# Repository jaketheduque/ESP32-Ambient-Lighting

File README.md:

Check out the project website here: https://jaketheduque.github.io/ESP32-Ambient-Lighting/

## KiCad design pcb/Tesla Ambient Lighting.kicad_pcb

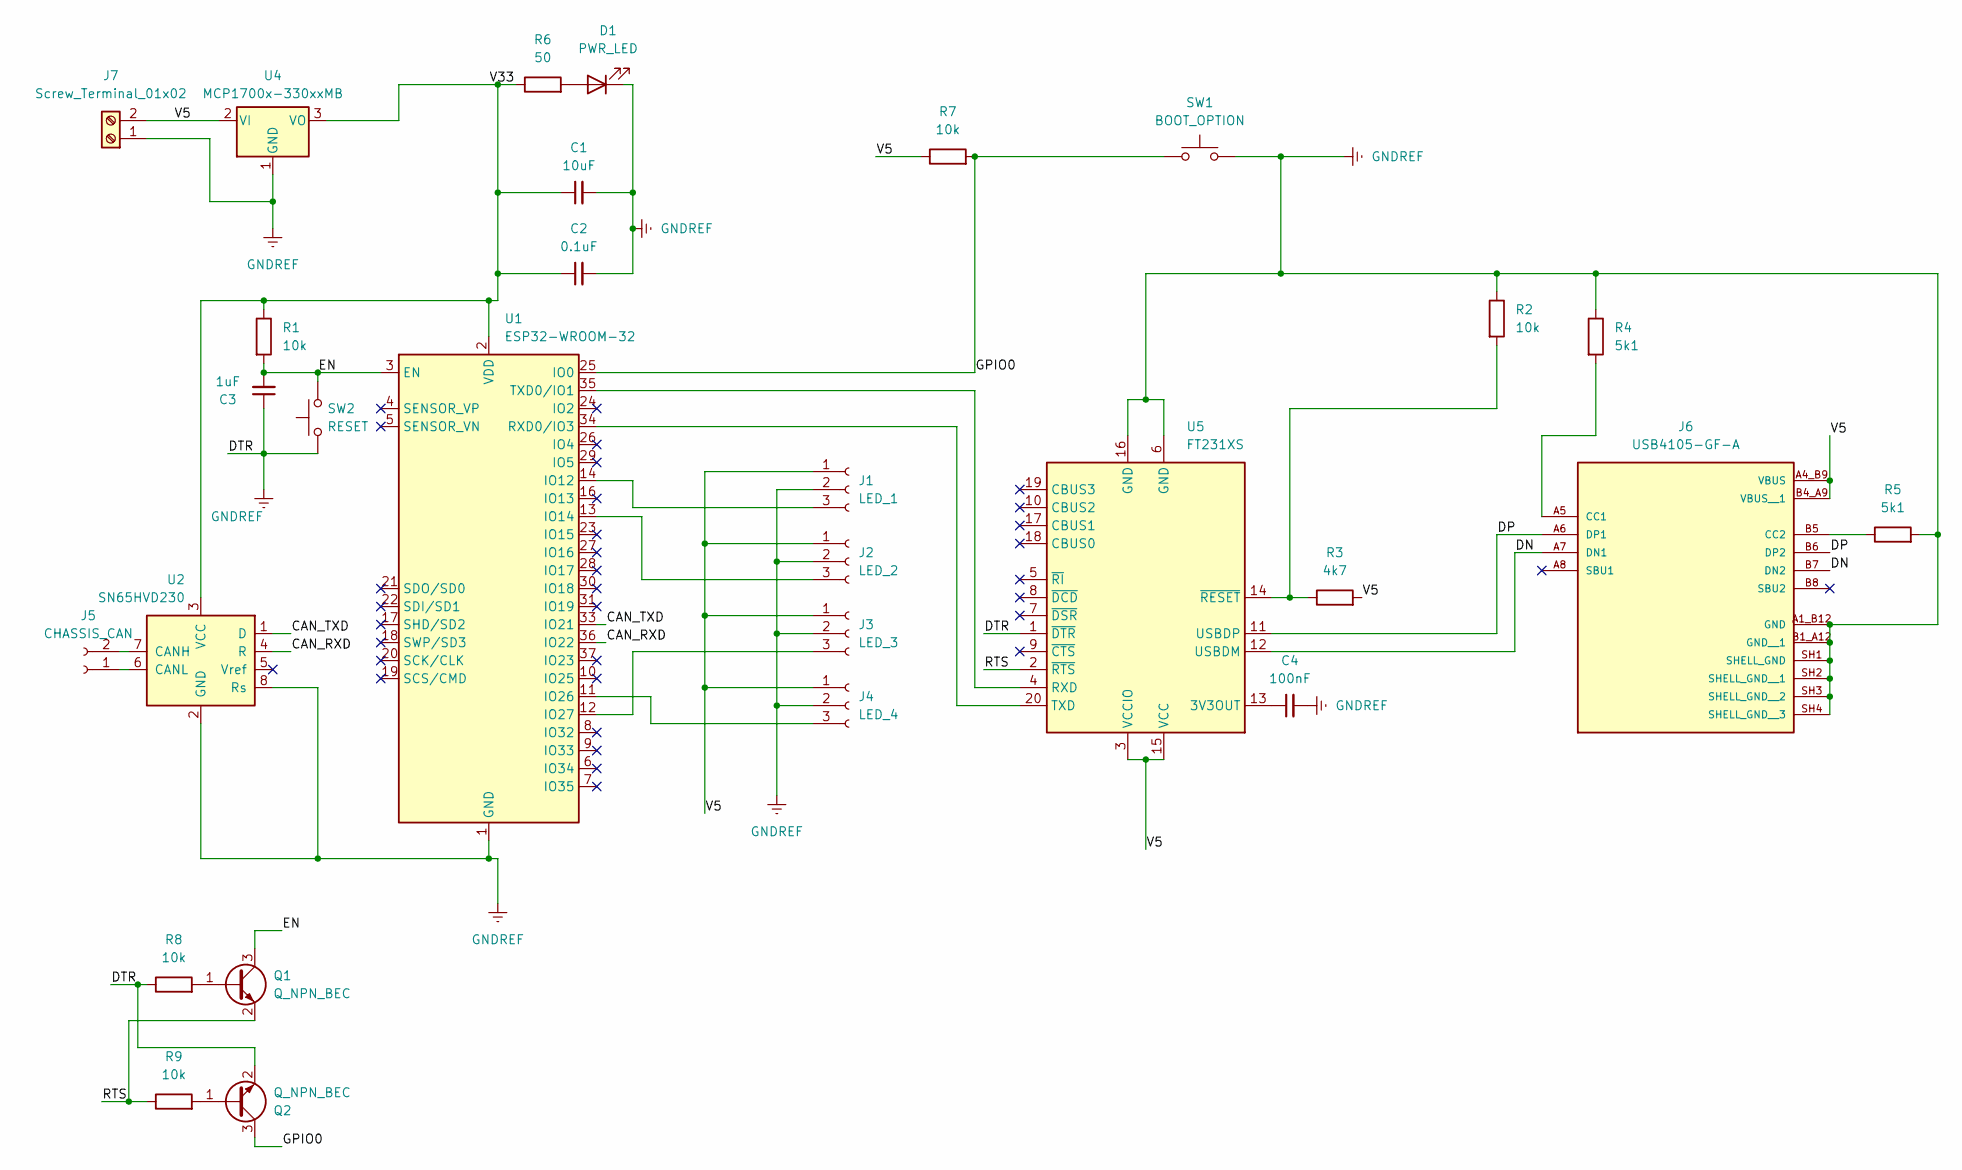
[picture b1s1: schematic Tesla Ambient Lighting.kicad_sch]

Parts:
C1: 10uF; C_0805_2012Metric
C2: 0.1uF; C_0805_2012Metric
C3: 1uF; C_0805_2012Metric
C4: 100nF; C_0805_2012Metric
D1: PWR_LED; LED_0805_2012Metric
J1: LED_1; JST_XH_S3B-XH-A_1x03_P2.50mm_Horizontal
J2: LED_2; JST_XH_S3B-XH-A_1x03_P2.50mm_Horizontal
J3: LED_3; JST_XH_S3B-XH-A_1x03_P2.50mm_Horizontal
J4: LED_4; JST_XH_S3B-XH-A_1x03_P2.50mm_Horizontal
J5: CHASSIS_CAN; JST_XH_S2B-XH-A_1x02_P2.50mm_Horizontal
J6: USB4105-GF-A; GCT_USB4105-GF-A; PARTREV B4
J7: Screw_Terminal_01x02; TerminalBlock_TE_282834-2_1x02_P2.54mm_Horizontal
Q1, Q2: Q_NPN_BEC; SOT-23
R1, R2, R7, R8, R9: 10k; R_0805_2012Metric
R3: 4k7; R_0805_2012Metric
R4, R5: 5k1; R_0805_2012Metric
R6: 50; R_0805_2012Metric
SW1: BOOT_OPTION; SW_SPST_B3U-1100P
SW2: RESET; SW_SPST_B3U-1100P
U1: ESP32-WROOM-32; ESP32-WROOM-32E
U2: SN65HVD230; SOIC-8_3.9x4.9mm_P1.27mm
U4: MCP1700x-330xxMB; SOT-89-3
U5: FT231XS; SSOP-20_3.9x8.7mm_P0.635mm

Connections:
/CAN_RXD: U1.36 (IO22), U2.4 (R)
/CAN_TXD: U1.33 (IO21), U2.1 (D)
/DN: J6.A7 (DN1), J6.B7 (DN2), U5.12 (USBDM)
/DP: J6.A6 (DP1), J6.B6 (DP2), U5.11 (USBDP)
/EN: C3.2, Q1.3 (C), R1.2, SW2.2, U1.3 (EN); also elsewhere on the board
/GPIO0: Q2.3 (C), R7.2, SW1.1, U1.25 (IO0)
/RTS: Q1.2 (E), R9.1, U5.2 (~RTS)
/V5: J1.1, J2.1, J3.1, J4.1, J6.A4_B9 (VBUS), J6.B4_A9 (VBUS__1), J7.2, R3.2, R7.1, U4.2 (VI), U5.3 (VCCIO), U5.15 (VCC)
/V33: C1.1, C2.1, R1.1, R6.1, U1.2 (VDD), U2.3 (VCC), U4.3 (VO)
GNDREF: C1.2, C2.2, C3.1, C4.2, D1.1 (K), J1.2, J2.2, J3.2, J4.2, J6.A1_B12 (GND), J6.B1_A12 (GND__1), J6.SH1 (SHELL_GND), J6.SH2 (SHELL_GND__1), J6.SH3 (SHELL_GND__2), J6.SH4 (SHELL_GND__3), J7.1, Q2.2 (E), R2.1, R4.1, R5.2, R8.1, SW1.2, SW1.3, SW2.1, U1.1 (GND), U1.15 (GND), U1.38 (GND), U1.39 (GND), U2.2 (GND), U2.8 (Rs), U4.1 (GND), U5.1 (~DTR), U5.6 (GND), U5.16 (GND); also elsewhere on the board
unnamed 10: D1.2 (A), R6.2; also elsewhere on the board
unnamed: J1.3, U1.14 (IO12)
unnamed: J2.3, U1.13 (IO14)
unnamed: J3.3, U1.12 (IO27)
unnamed: J4.3, U1.11 (IO26)
unnamed: J5.1, U2.6 (CANL)
unnamed: J5.2, U2.7 (CANH)
unnamed: J6.A5 (CC1), R4.2
unnamed: J6.B5 (CC2), R5.1
unnamed: Q1.1 (B), R8.2
unnamed: Q2.1 (B), R9.2
unnamed: U1.34 (RXD0/IO3), U5.20 (TXD)
unnamed: U1.35 (TXD0/IO1), U5.4 (RXD)
unnamed: C4.1, U5.13 (3V3OUT)
unnamed: R2.2, R3.1, U5.14 (~RESET)

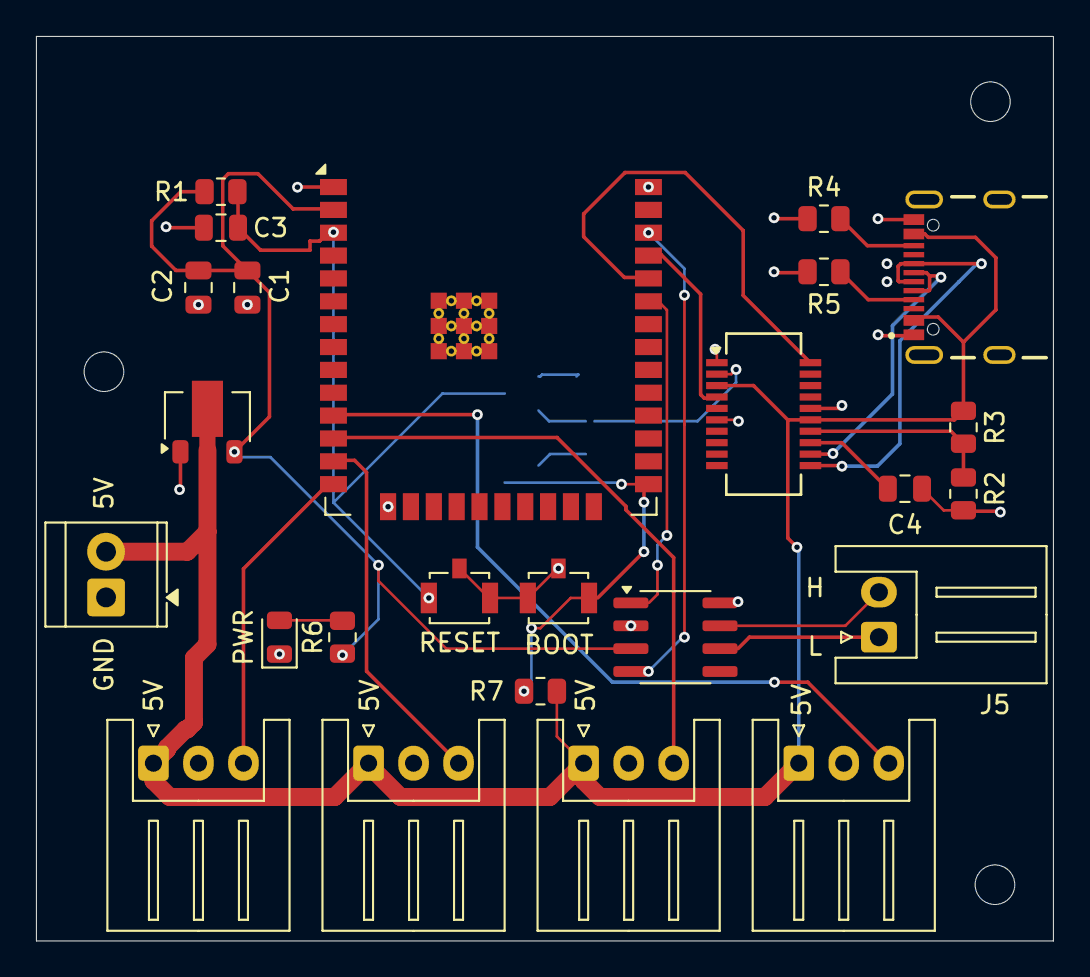
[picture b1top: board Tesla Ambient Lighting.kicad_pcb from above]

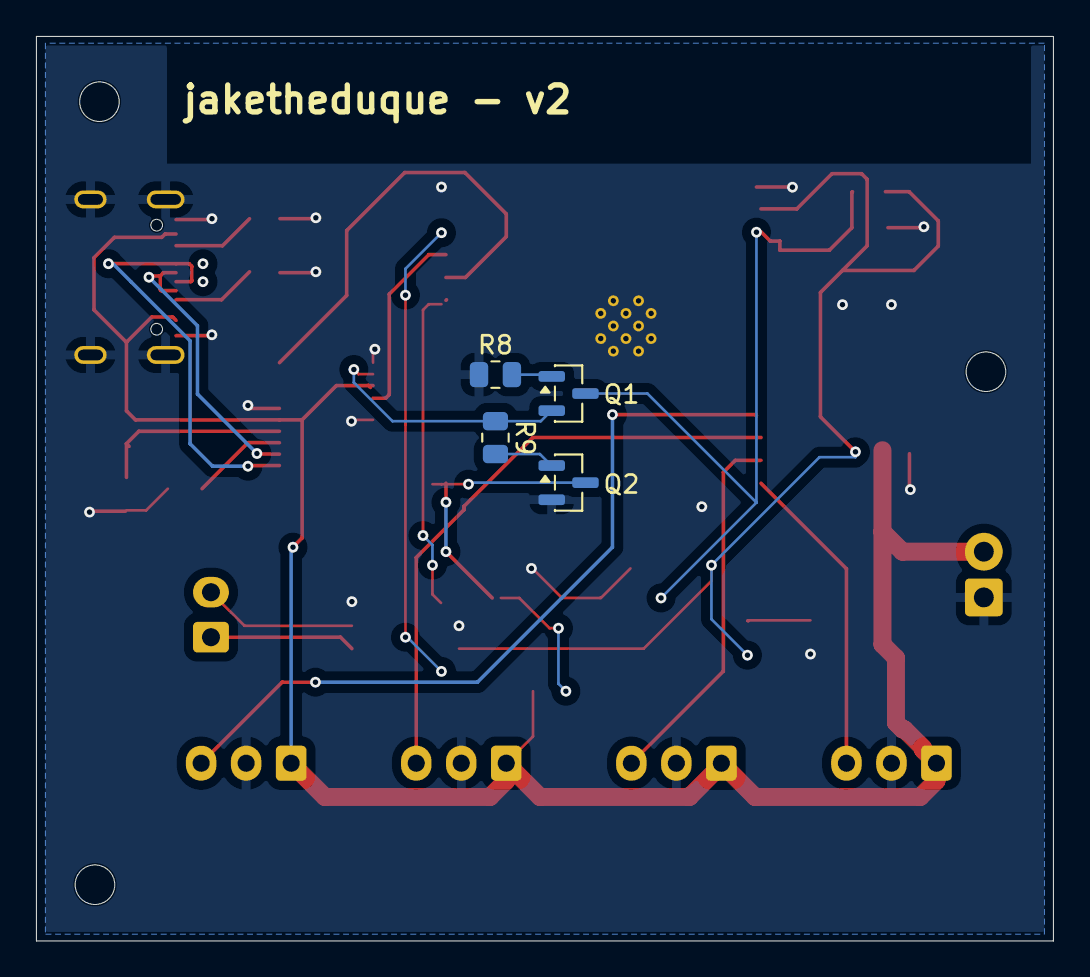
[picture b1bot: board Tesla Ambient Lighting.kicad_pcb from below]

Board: 2 copper layers, 56.5 x 50.2 mm, 29 parts (4 on the bottom side), 25 nets.

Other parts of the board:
PWR: PWR_LED; LED_0805_2012Metric
RESET: RESET; SW_SPST_B3U-1100P

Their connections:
/EN: RESET.2; also elsewhere on the board
GNDREF: PWR.1 (K), RESET.1, RESET.3; also elsewhere on the board
unnamed 10: PWR.2 (A); also elsewhere on the board

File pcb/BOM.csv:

"Id";"Designator";"Footprint";"Quantity";"Designation";"Supplier and ref";
1;"J6";"GCT_USB4105-GF-A";1;"USB4105-GF-A";;;
2;"U2";"SOIC-8_3.9x4.9mm_P1.27mm";1;"SN65HVD230";;;
3;"Q2,Q1";"SOT-23";2;"Q_NPN_BEC";;;
4;"R8,R9,R1,R2,R7";"R_0805_2012Metric";5;"10k";;;
5;"PWR";"LED_0805_2012Metric";1;"PWR_LED";;;
6;"U5";"SSOP-20_3.9x8.7mm_P0.635mm";1;"FT231XS";;;
7;"J5";"JST_XH_S2B-XH-A_1x02_P2.50mm_Horizontal";1;"CHASSIS_CAN";;;
8;"U4";"SOT-89-3";1;"MCP1700x-330xxMB";;;
9;"C4";"C_0805_2012Metric";1;"100nF";;;
10;"R6";"R_0805_2012Metric";1;"50";;;
11;"R5,R4";"R_0805_2012Metric";2;"5k1";;;
12;"RESET";"SW_SPST_B3U-1100P";1;"RESET";;;
13;"SW1";"SW_SPST_B3U-1100P";1;"BOOT_OPTION";;;
14;"J3";"JST_XH_S3B-XH-A_1x03_P2.50mm_Horizontal";1;"LED_3";;;
15;"C1";"C_0805_2012Metric";1;"10uF";;;
16;"J2";"JST_XH_S3B-XH-A_1x03_P2.50mm_Horizontal";1;"LED_2";;;
17;"J7";"TerminalBlock_TE_282834-2_1x02_P2.54mm_Horizontal";1;"Screw_Terminal_01x02";;;
18;"C3";"C_0805_2012Metric";1;"1uF";;;
19;"U1";"ESP32-WROOM-32E";1;"ESP32-WROOM-32";;;
20;"J4";"JST_XH_S3B-XH-A_1x03_P2.50mm_Horizontal";1;"LED_4";;;
21;"R3";"R_0805_2012Metric";1;"4k7";;;
22;"C2";"C_0805_2012Metric";1;"0.1uF";;;
23;"J1";"JST_XH_S3B-XH-A_1x03_P2.50mm_Horizontal";1;"LED_1";;;

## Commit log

2025-06-02 added sequential animation command for ambient_light_t
2025-06-02 wrote untested code for CAN bus light control
2025-06-03 added fade animation and tested CAN code
2025-06-04 removed README.md to be replaced later
2025-06-06 changed ambient lighting commands to listen to ambient lighting CAN messages
2025-06-08 current color shared globally
2025-06-13 removed center light
2025-06-17 fixed semaphore initialization so that it is not blocking tasks
2025-07-14 changed control logic for lights
2025-08-06 fixed display CAN mask
2025-08-06 removed current_color from ambient_light_t and updated commands
2025-08-11 added index.md for GitHub project page
2025-08-11 renamed page directory to docs
2025-08-11 added details about light control logic
2025-08-11 fixed light control logic
2025-08-14 added OTA software updates; updates to light states
2025-08-14 fixed control logic to correctly set light state to OFF; added script for sending OTA update
2025-08-27 fixed image links
2025-08-28 OTA section added to documentation
2025-11-21 Added animation video
2025-11-22 added video demo
2025-11-22 removed markdown page
2025-11-22 added HTML page
2025-11-22 added source code link
2026-01-12 added PCB files
2026-01-16 started PCB V2; adding DTR and RTS control pins, RST button, and power LED; also wanting to add serial LED
2026-01-19 updated pcb to have RST button, power LED, and flow control
2026-01-19 generate jlcpcb plots
2026-01-19 added new command for setting color; color input for website; lights automatically change on form submit
2026-03-03 added functions to flush a command queue and recover TWAI
2026-03-03 changed queue send calls to be non-blocking
2026-03-03 added flush calls
2026-03-03 small formatting changes
2026-03-03 fixed fade to command
2026-03-03 added CAN message mask
